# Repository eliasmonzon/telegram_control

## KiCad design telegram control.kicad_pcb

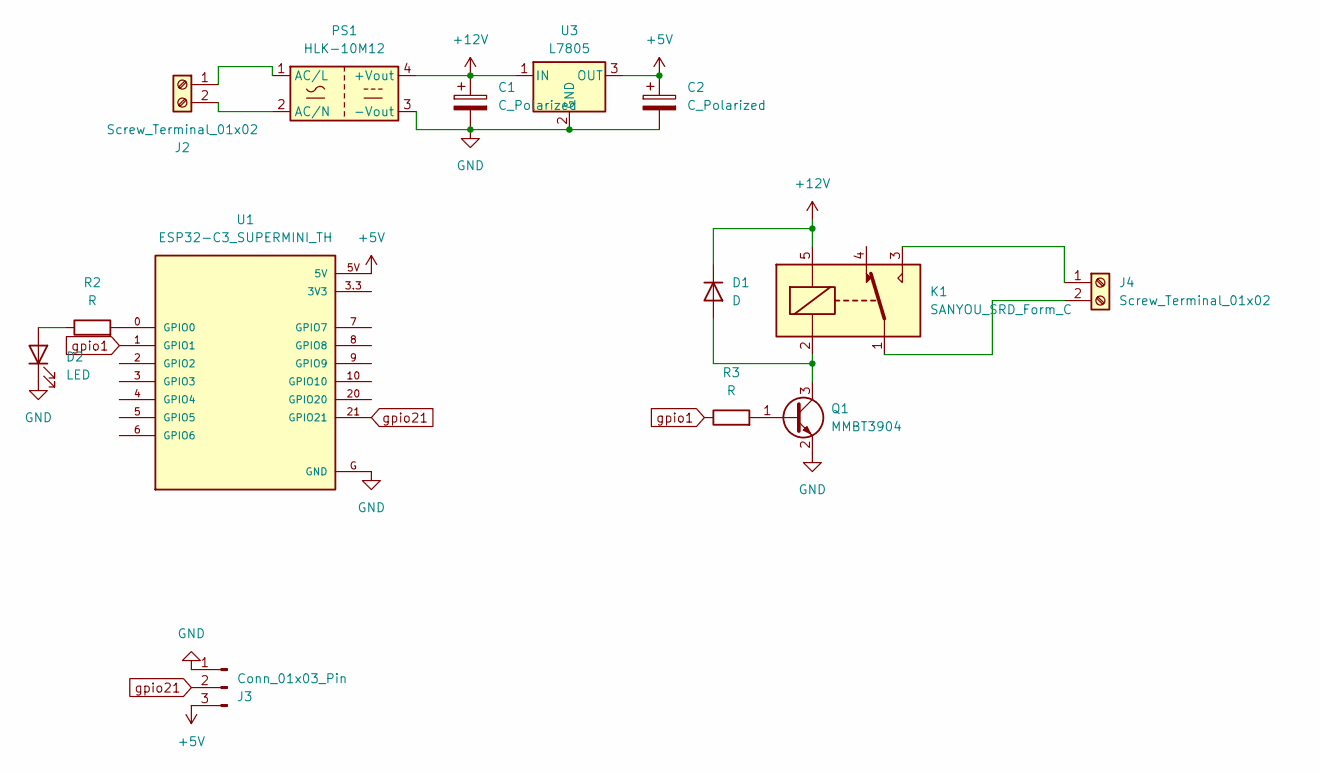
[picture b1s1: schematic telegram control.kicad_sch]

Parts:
C1, C2: C_Polarized; CP_Radial_D4.0mm_P1.50mm
D1: D; D_1206_3216Metric
D2: LED; LED_D3.0mm
J2, J4: Screw_Terminal_01x02; TerminalBlock_Phoenix_MKDS-1,5-2_1x02_P5.00mm_Horizontal
J3: Conn_01x03_Pin; PinHeader_1x03_P2.54mm_Vertical
K1: SANYOU_SRD_Form_C; Relay_SPDT_SANYOU_SRD_Series_Form_C
PS1: HLK-10M12; Converter_ACDC_Hi-Link_HLK-PMxx
Q1: MMBT3904; SOT-23
R2, R3: R; R_1206_3216Metric
U1: ESP32-C3_SUPERMINI_TH; MODULE_ESP32-C3_SUPERMINI_TH
U3: L7805; TO-252-2

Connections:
+5V: C2.1, J3.3, U1.5V, U3.3 (OUT)
+12V: C1.1, D1.1 (K), K1.5, PS1.4 (+Vout), U3.1 (IN)
GND: C1.2, C2.2, D2.1 (K), J3.1, PS1.3 (-Vout), Q1.2 (E), U1.G (GND), U3.2 (GND)
unnamed: D1.2 (A), K1.2, Q1.3 (C)
unnamed: D2.2 (A), R2.1
unnamed: J2.1, PS1.1 (AC/L)
unnamed: J2.2, PS1.2 (AC/N)
unnamed: J4.1, K1.3
unnamed: J4.2, K1.1
unnamed: Q1.1 (B), R3.2
unnamed: R2.2, U1.0 (GPIO0)
gpio1: R3.1, U1.1 (GPIO1)
gpio21: J3.2, U1.21 (GPIO21)

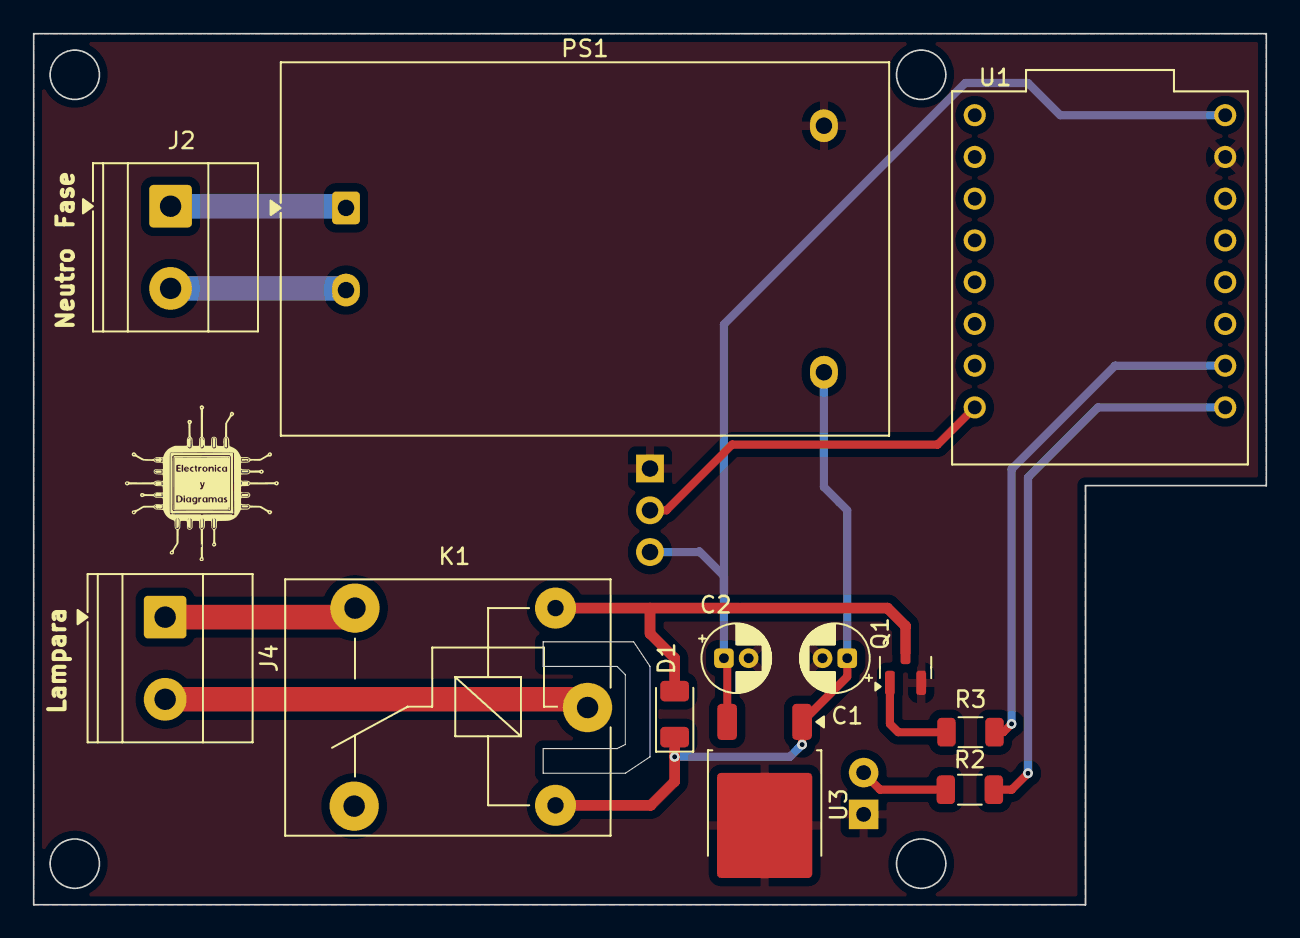
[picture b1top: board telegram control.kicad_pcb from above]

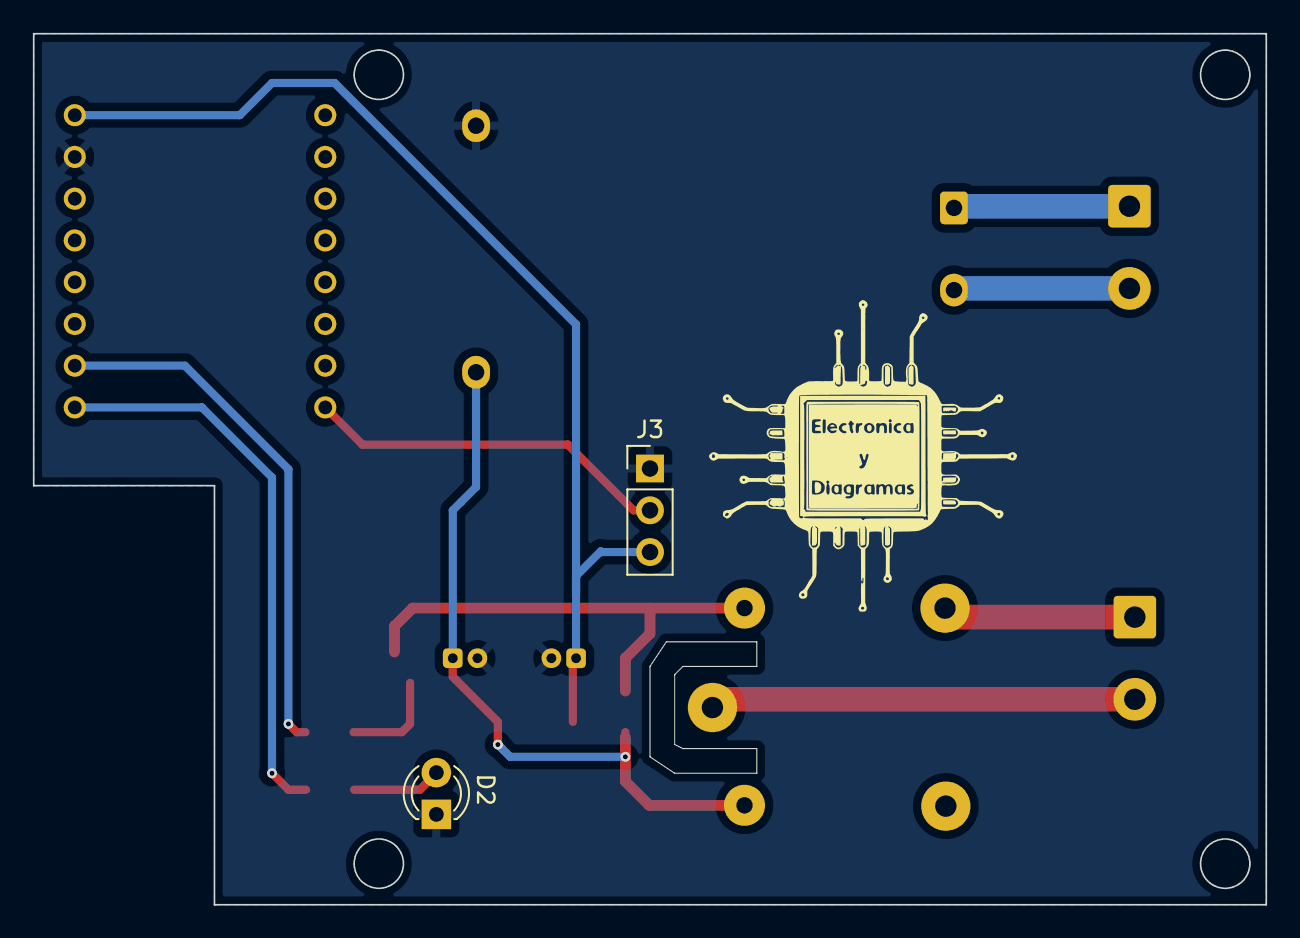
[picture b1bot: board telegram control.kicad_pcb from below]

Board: 2 copper layers, 75.0 x 53.0 mm, 14 parts (2 on the bottom side), 13 nets.

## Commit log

2025-07-23 telegram_control
2025-07-24 control por telegram
